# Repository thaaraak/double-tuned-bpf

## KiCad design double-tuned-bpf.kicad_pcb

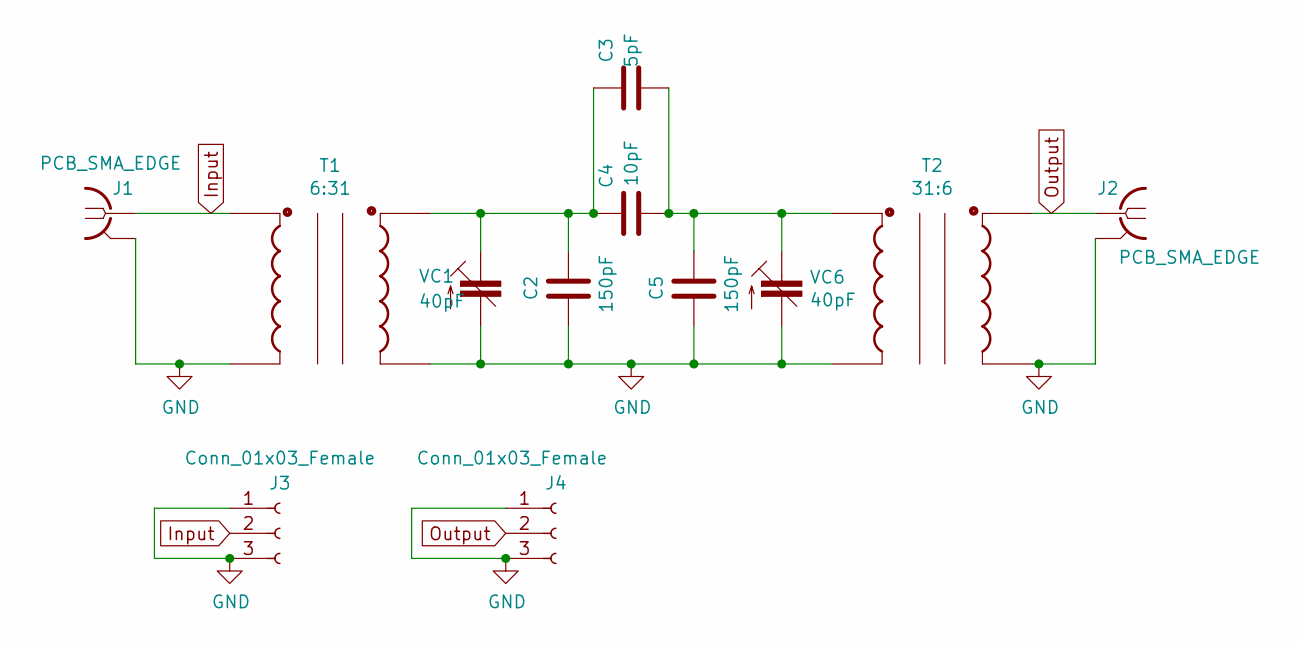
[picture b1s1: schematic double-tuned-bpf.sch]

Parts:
C2, C5: 150pF; Capacitor 1206
C3: 5pF; Capacitor 1206
C4: 10pF; Capacitor 1206
J1, J2: PCB_SMA_EDGE; PCB-SMA-EDGE
J3, J4: Conn_01x03_Female; PinHeader_1x03_P2.54mm_Vertical
T1: 6:31; T37 Transformer
T2: 31:6; T37 Transformer
VC1, VC6: 40pF; trimcap

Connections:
GND: C2.1, C5.1, J1.2, J2.2, J3.1, J3.3, J4.1, J4.3, T1.C1A, T1.C2A, T2.C1A, T2.C2A, VC1.2 (A), VC6.2 (A)
Input: J1.1, J3.2, T1.C1B
unnamed: C2.2, C3.1, C4.1, T1.C2B, VC1.1 (E)
unnamed: C3.2, C4.2, C5.2, T2.C1B, VC6.1 (E)
Output: J2.1, J4.2, T2.C2B

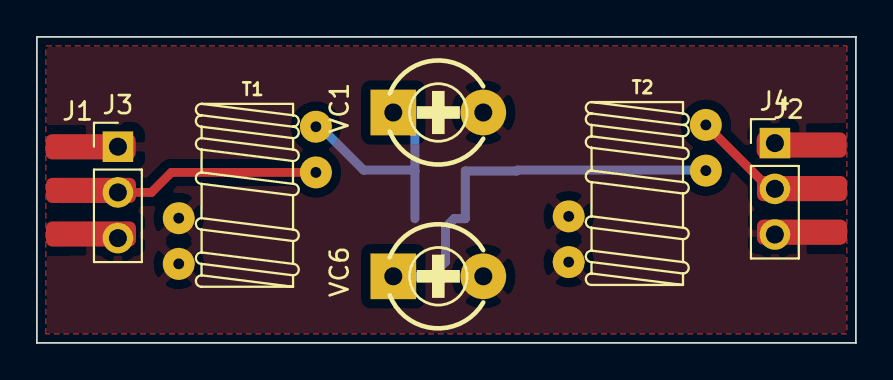
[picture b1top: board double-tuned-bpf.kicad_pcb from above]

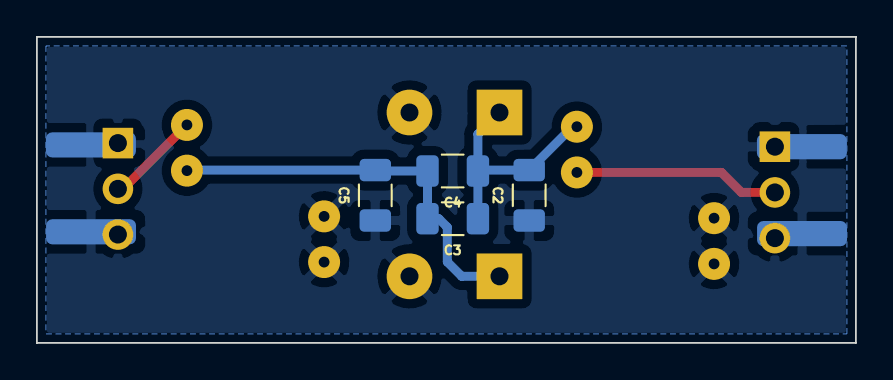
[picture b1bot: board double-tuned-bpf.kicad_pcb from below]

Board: 2 copper layers, 45.5 x 17.0 mm, 12 parts (4 on the bottom side), 5 nets.

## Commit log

2022-12-23 Update fp-info-cache
